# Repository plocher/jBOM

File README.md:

# jBOM — KiCad Bill of Materials and Placement Generator

## Why jBOM?

Designing a PCB in KiCad is only part of the journey that results in a fabricated and assembled electronic product.  PCB fabrication requires Gerber files; assembly requires a **Bill of Materials (BOM)** and a **Placement file (CPL/POS)**.  jBOM generates all three.

The common KiCad workflow has you annotate your KiCad symbols with supply chain details such as "IPN:RES-331-0603", "MFG:Yageo", "MPN:CC0603KRX7R9BB104", "LCSC:C123456", and then use KiCad's fabrication plugins to generate BOM and CPL files.  This mechanism is easy to understand, and, through KiCad's web/database library integration, plugins such as Part-DB, InvenTree, PartsBox and GitPLM connect to extensive parts databases.  While these this workflow has proven sufficient for many developers, it inadvertently makes it difficult to decouple supply chain evolution from a project's electronic and mechanical specifications.

**jBOM solves this** by separating part selection from circuit design. You design with generic values ("10k, 5%, Resistor_SMD:R_0603_1608Metric"), maintain a currated inventory file with your desired parts, and jBOM intelligently matches them at BOM generation time.  Changing suppliers or cost reducing a set of projects is as simple as updating an inventory spreadsheet.

## Documentation
Command line: [docs/README.man1.md](docs/README.man1.md)
Python Library API: [docs/README.man3.md](docs/README.man3.md)
KiCad Eeschema Integration: [docs/README.man4.md](docs/README.man4.md)
jBOM Inventory File Format: [docs/README.man5.md](docs/README.man5.md)

## Installation
Requires Python 3.10 or newer.

**From PyPI (recommended):**

```bash
# Basic installation (with only CSV inventory support)
pip install jbom

# With CSV, Excel and Numbers spreadsheet support
pip install jbom[all]

# With CSV and Excel support
pip install jbom[excel]
# With CSV and Apple Numbers support
pip install jbom[numbers]

# With Mouser Search support
pip install jbom[search]
```

## Quick Start

**Scenario: New KiCad project → JLCPCB manufacturing files.**

### 1. Extract an inventory template

```bash
jbom inventory MyProject/ -o inventory.csv
```

This writes one row per unique Value + Package combination found in your schematics. IPN, Category, Value, and Package are pre-filled; supplier columns (LCSC, Manufacturer, MFGPN) are blank for you to complete.

### 2. Audit schematic field quality

Before filling in part numbers, verify your schematic fields are complete:

```bash
jbom audit MyProject/ -o report.csv
```

This checks every component against jBOM's field taxonomy and writes findings to `report.csv`. Open it in a spreadsheet, fill in `ApprovedValue` for any `QUALITY_ISSUE` rows, set `Action` to `SET`, then apply the fixes back to your schematic:

```bash
jbom annotate MyProject/ --repairs report.csv
```

Once the schematic is clean, verify your inventory covers every component:

```bash
jbom audit MyProject/ --inventory inventory.csv
```

If your inventory carries `Datasheet`/`Datasheet Name` columns for a shared datasheet document library, `jbom audit` also runs read-only naming/provenance hygiene checks against them, and can check file presence against a local library checkout:

```bash
jbom audit inventory.csv --datasheet-library ~/Dropbox/workspace/SPCoast-inventory
```

To opt in to checking whether your inventory's Datasheet URLs still resolve (and get proposed upgrades for dead/impostor ones), pass `--check-urls`. This makes network requests and is off by default:

```bash
jbom audit inventory.csv --check-urls -o url_upgrades.csv
```

### 3. Fill in part numbers for JLC's LCSC supplier

An inventory file maps your generic schematic values to real parts from a supplier's catalog — in this case LCSC, which JLCPCB uses for sourcing. Open `inventory.csv` and fill in the **LCSC** column for each part you want JLCPCB to source. Set **Priority** to `1` on rows you want matched first.

To find LCSC part numbers:
- Search interactively: `jbom search "10k 0603 resistor" --supplier lcsc`
- Look up manually at [jlcpcb.com/parts](https://jlcpcb.com/parts)
- Export your JLCPCB private parts library (*User Center → My Inventory → My Parts Lib → Export*) and load it alongside: `--inventory project.csv --inventory jlc_library.xlsx`

> **Coming soon**: `jbom inventory MyProject/ --supplier lcsc --limit 3 -o inventory.csv` will search and populate part numbers automatically.

> **Curating a shared datasheet library?** Datasheet URLs encountered by `jbom search` / `jbom inventory --supplier` are automatically staged for review once you configure `datasheet_staging.staging_dir` in your own `~/.jbom/common.jbom.yaml`. `jbom inventory admit` is the gate that turns staged PDFs into a reviewed, named library: it proposes a manifest (curated name, matching inventory rows), you edit it, then `--apply` moves accepted PDFs into `datasheets/<name>.pdf` and hands back a paste-file for the `Datasheet Name` column. See [docs/reference/cli.md](docs/reference/cli.md#admit-subcommand-jbom-inventory-admit).

### 4. Generate fabrication files

Use `jbom fab` for a one-shot run that writes everything to a `production/` folder:

```bash
jbom fab MyProject/ --jlc --inventory inventory.csv
```

This produces:
```
production/
  jbom.csv                    ← BOM for JLCPCB
  cpl.csv                     ← component placement
  MyProject_1.0.zip           ← Gerber archive for upload (requires kicad-cli)
  backups/MyProject_1.0_....zip
```

Or generate files individually:
```bash
jbom bom MyProject/ --jlc --inventory inventory.csv   # writes MyProject.bom.csv
jbom pos MyProject/ --jlc                             # writes MyProject.pos.csv
jbom gerbers MyProject/ --jlc                         # writes gerbers/ (requires kicad-cli)
```
Preview without writing: `jbom bom MyProject/ --jlc --inventory inventory.csv -o console`

---

For the full step-by-step walkthrough, options, and troubleshooting tips, see the **[Tutorial series](docs/tutorial/README.md)**.

## KiCad Integration

jBOM provides a **Pcbnew ActionPlugin** (a toolbar button in the PCB editor) that generates BOM, pick-and-place (CPL), and Gerbers in one click. The plugin is distributed through KiCad's **Plugin and Content Manager (PCM)** as a separate channel from PyPI; `pip install jbom` installs the CLI and library only and does **not** register the KiCad plugin.

To install the plugin:

1. Download the latest PCM archive from GitHub's stable-name URL:
   [`https://github.com/plocher/jBOM/releases/latest/download/jbom-pcm.zip`](https://github.com/plocher/jBOM/releases/latest/download/jbom-pcm.zip)
   (GitHub redirects `releases/latest/download/<asset>` to whatever asset of that name is attached to the newest release, so the URL never needs to be edited when a new version ships.)
2. In KiCad, open **Plugin and Content Manager**, choose **Install from File…**, and select the downloaded `jbom-pcm.zip`.
3. Open the **PCB Editor** (Pcbnew); the jBOM toolbar button appears automatically. Vendored runtime dependencies ship inside the archive, so no additional `pip install` step is required inside KiCad's bundled Python.

For fabricator flags, output columns, inventory requirements, custom fabricator configuration, and troubleshooting, see [docs/reference/kicad-plugin.md](docs/reference/kicad-plugin.md).

**Legacy Eeschema BOM wrapper.** The repo also ships `kicad_jbom_plugin.py`, a thin shim that lets Eeschema's **Tools → Generate BOM** dialog call `jbom bom` for schematic-only BOM output. This path is optional and requires a one-time manual registration via Eeschema's Add-plugin dialog. See the [kicad-plugin-setup skill](.agents/skills/kicad-plugin-setup/SKILL.md) if you need it. Most users should use the PCM ActionPlugin above instead.

## Configuration

Built-in fabricator profiles: `--jlc`, `--pcbway`, `--seeed`.

To create a custom profile or configure organisation-wide defaults, see [docs/tutorial/README.documentation.md](docs/tutorial/README.documentation.md) and [docs/README.configuration.md](docs/README.configuration.md).

## Contributing

Contributions are welcome! jBOM is developed on GitHub at [github.com/plocher/jBOM](https://github.com/plocher/jBOM).

To contribute:
1. Fork the repository
2. Create a feature branch
3. Run tests locally:
   - Fast canary: `PYTHONPATH=src python -m pytest tests/unit/test_cli_help.py tests/unit/test_unified_loader.py tests/unit/test_fabricator_config_schema.py tests/unit/test_supplier_config_schema.py -q` and `PYTHONPATH=src python -m behave --format progress features/cli/basics.feature features/project/file.feature features/bom/core.feature features/pos/core.feature features/inventory/core.feature features/audit/core.feature`
   - Comprehensive: `PYTHONPATH=src python -m pytest tests/ -v` and `PYTHONPATH=src python -m behave --format progress features/`
4. Submit a pull request

Regenerate deterministic search parity artifacts (fixture-based):
`python scripts/generate_search_parity_artifacts.py`

Regenerate baseline-vs-candidate parity delta evidence:
`python scripts/generate_search_parity_delta_report.py`

See [docs/CONTRIBUTING.md](docs/CONTRIBUTING.md) for details.

**License**: MIT — See LICENSE file for full terms.
Author: John Plocher

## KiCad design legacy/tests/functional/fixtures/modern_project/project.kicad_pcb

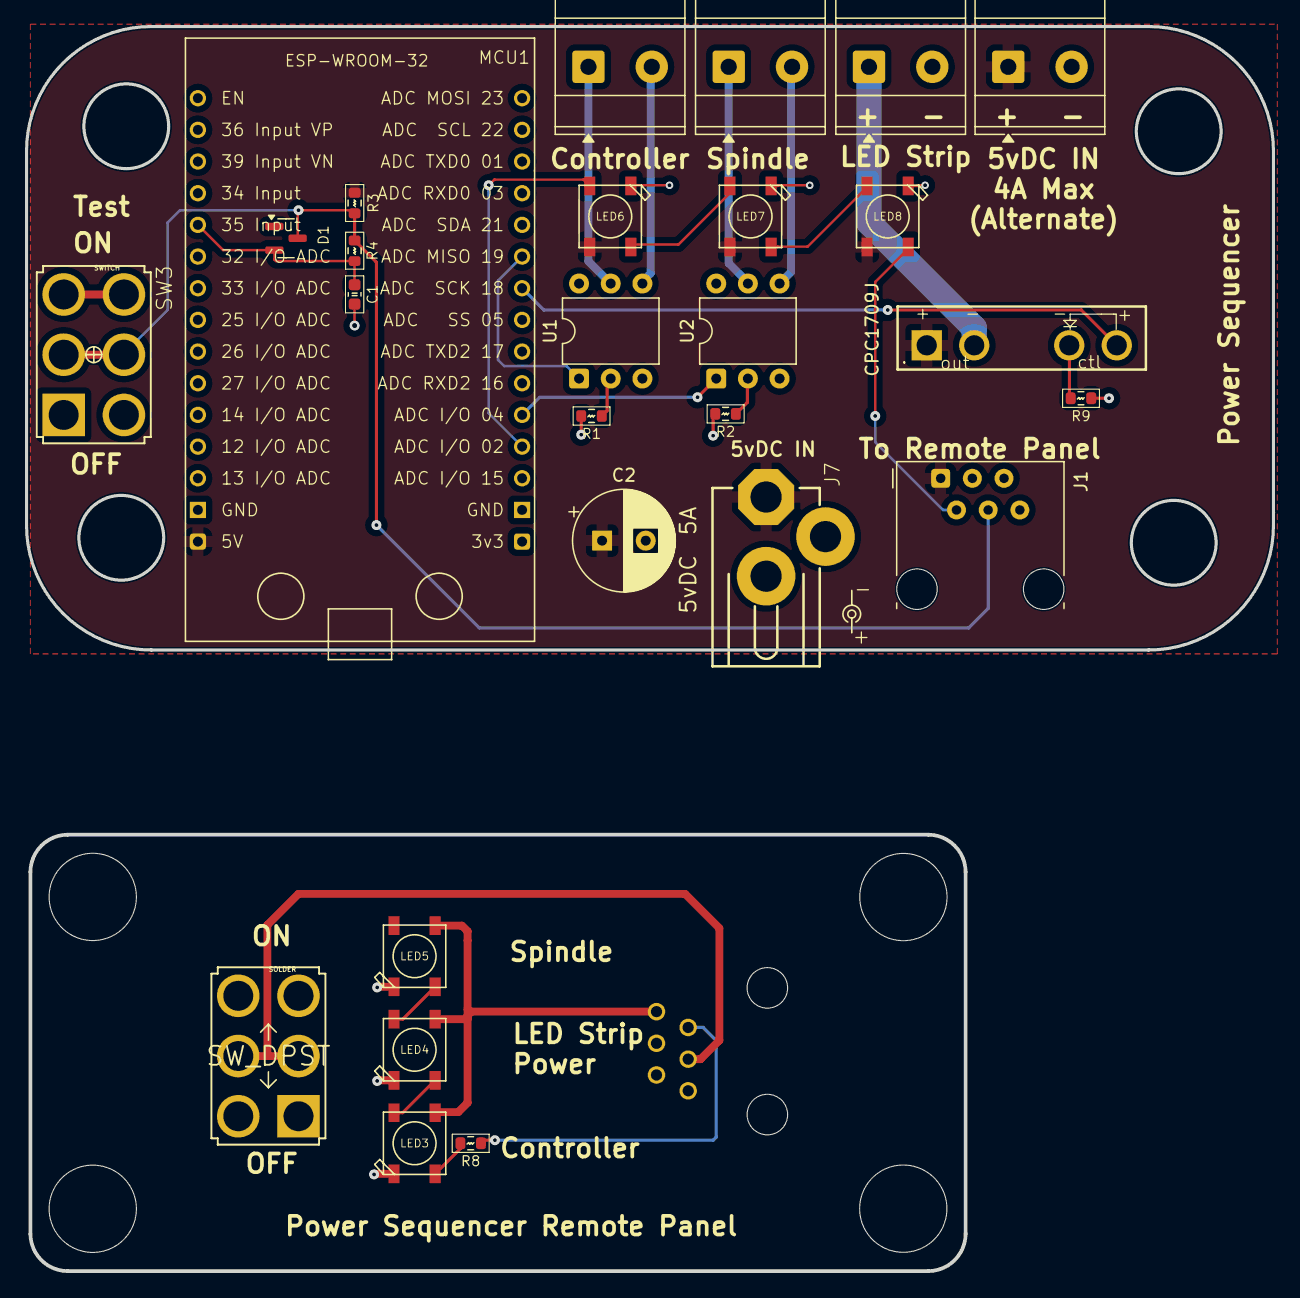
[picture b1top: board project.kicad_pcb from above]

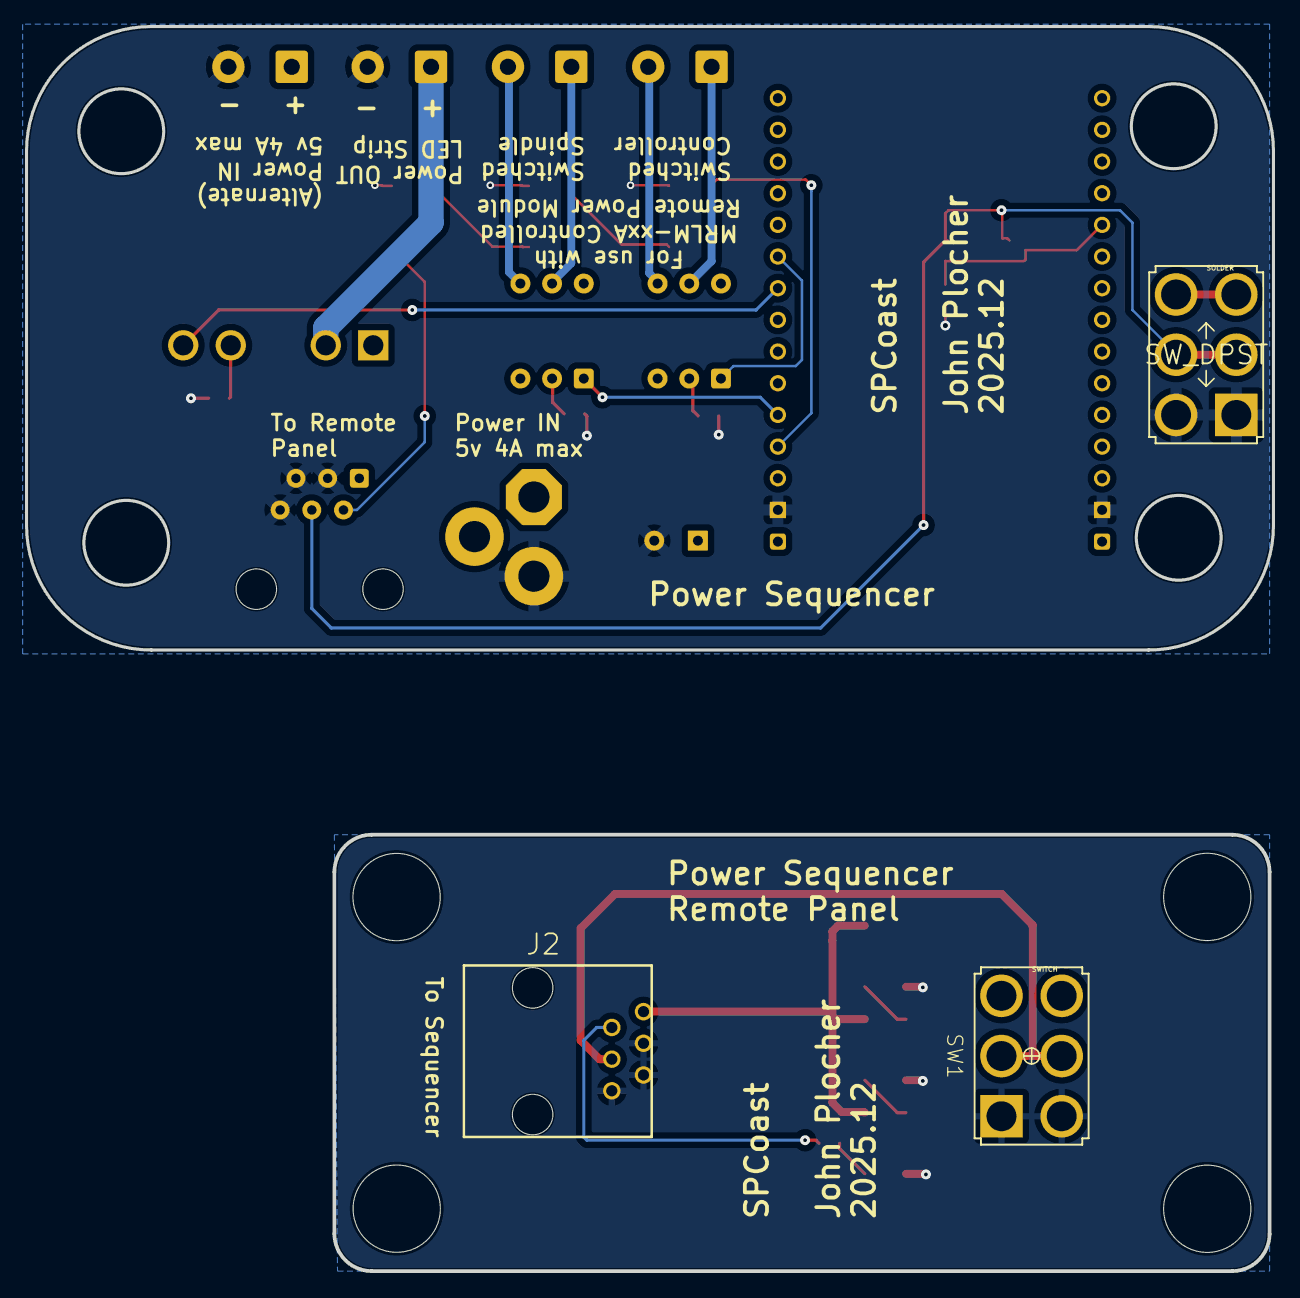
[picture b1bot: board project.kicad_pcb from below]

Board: 2 copper layers, 100.0 x 99.8 mm, 29 parts (2 on the bottom side), 26 nets.

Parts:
Board1: Board_100x050
C1: 1.0uF; 0603-CAP
C2: 1000uF; CP_Radial_D8.0mm_P3.50mm
D1: BAT54A; SOT-23
J1: Conn_6P6C; RJ12_Amphenol_54601-x06_Horizontal
J2: Conn_6P6C; RJ12_TOP
J5, J6, J8, J9: Conn_01x02; TerminalBlock_Phoenix_MKDS-3-2-5.08_1x02_P5.08mm_Horizontal
J7: DCJ0202
K1: CPC1709J; Relay_CPC1709J
LED3, LED4, LED5, LED6, LED7, LED8: WS2812B
MCU1: ESP32-DevKit-V1; ESP32_DevKit_V1
R1, R2, R8, R9: 330Ω; 0603-RES
R3: 10k0Ω; 0603-RES
R4: 22k0Ω; 0603-RES
SW1, SW3: SW_DPST; DPDT.LUGS
U1, U2: 4N28; DIP-6_W7.62mm

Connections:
+5V: C2.1, J1.1, J7.1, J9.1, K1.1 (+_1), LED6.1-VDD (VDD), LED7.1-VDD (VDD), LED8.1-VDD (VDD), MCU1.5V (+5V), R3.1
/5v: J2.1, LED3.1-VDD (VDD), LED4.1-VDD (VDD), LED5.1-VDD (VDD)
GND: C1.2, C2.2, J1.3, J1.5, J1.6, J2.3, J2.5, J2.6, J7.3, J8.2, J9.2, LED3.3-GND (GND), LED4.3-GND (GND), LED5.3-GND (GND), LED6.3-GND (GND), LED7.3-GND (GND), LED8.3-GND (GND), MCU1.GND, MCU1.GND@1 (GND), R1.2, R2.2, R9.1, SW1.1 (A), SW1.4 (A), SW3.1 (A), SW3.4 (A)
unnamed: J5.1, U2.5
unnamed: J5.2, U2.4
unnamed: J6.1, U1.5
unnamed: J6.2, U1.4
unnamed: J8.1, K1.2 (-_1)
unnamed: K1.3 (-_2), R9.2
unnamed: LED3.4-DIN (DI), R8.2
unnamed: LED3.2-DOUT (DO), LED4.4-DIN (DI)
unnamed: LED4.2-DOUT (DO), LED5.4-DIN (DI)
unnamed: LED6.2-DOUT (DO), LED7.4-DIN (DI)
unnamed: LED7.2-DOUT (DO), LED8.4-DIN (DI)
unnamed: R1.1, U1.2
unnamed: R2.1, U2.2
unnamed: SW3.3 (C), SW3.6 (C)
_neopixel: J2.2, R8.1
_switch: J2.4, SW1.2 (B), SW1.5 (B)
controller: MCU1.IO19 (GPIO19), U1.1
debounced_switch: C1.1, D1.2, MCU1.IO35 (GPIO35), R4.2
neopixel: LED6.4-DIN (DI), MCU1.IO2 (GPIO2)
neopixel_out: J1.2, LED8.2-DOUT (DO)
spindle: MCU1.IO4 (GPIO4), U2.1
ssr: K1.4 (+_2), MCU1.IO18 (GPIO18)
switch: D1.3, J1.4, R3.2, R4.1, SW3.2 (B), SW3.5 (B)

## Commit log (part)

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2026-05-09 fix(plugin): skip gerbers, use pcbnew title block directly, surface config error
    Three smoke-test fixes:
    - skip_gerbers=True: running kicad-cli subprocess from inside a KiCad plugin
    causes a hang on macOS (two KiCad instances conflict). Gerbers disabled until
    native pcbnew PLOT_CONTROLLER path is implemented.
    - Archive name: use pcbnew.GetBoard().GetTitleBlock() directly instead of
    reading from disk — faster and avoids kicad_pro filename guessing.
2026-05-09 fix(discovery): prefer directory-name .kicad_pro when multiple exist
    When a project directory contains multiple .kicad_pro files (e.g. a main
    project alongside a sub-project or variant), prefer the file whose stem
    matches the directory name — the canonical KiCad convention.
    Falls back to alphabetically first when no directory-name match exists.
    This fixes POS (CPL) generation in projects with multi-.kicad_pro dirs,
    unblocking cpl.csv output in the KiCad plugin smoke test.
2026-05-09 fix(plugin): wx.Dialog+Show() for toolbar re-invoke; Finder opens in debug mode
    Bug 1 — Finder not opening when debug=True then Close:
    _on_complete stay_open branch bound Close to lambda _e: self.Destroy()
    without calling _open_folder first. Replace with _close_and_open() closure
    that honours open_folder before destroying.
    Bug 2 — toolbar button only works once:
    wx.Frame.__init__ creates a wxFrame C++ object; KiCad's plugin framework
2026-05-10 feat(plugin): Session A POC — loadable stub ActionPlugin, options, PCM builder (#227)
    Implements issue #227 Session A scope:
    - src/jbom/plugin/__init__.py: FT-style guard registers ActionPlugin only
    inside KiCad (pcbnew in sys.modules). Safe no-op in CLI / test environments.
    sys.path bootstrap supports both PCM install (vendored jbom/) and dev-loop
    (symlink src/jbom/plugin → com_spcoast_jbom in KiCad scripting folder).
    - src/jbom/plugin/plugin.py: JBOMFabricationPlugin(pcbnew.ActionPlugin)
2026-05-10 6.55.0
    Automatically generated by python-semantic-release
2026-05-10 fix(plugin): eliminate SWIG reads + restore plot dir + auto-save after Gerbers (#255) (#258)
    * refactor(plugin): eliminate SWIG reads from archive template expansion (#255)
    Replace board.GetProject() / board.GetTitleBlock() SWIG calls with
    file-based reads in both plugin.py and dialog.py.
    Background: The dirty flag (*) appearing on ActionPlugin toolbar invocation
    is a KiCad 10 framework behavior — the C++ ActionPlugin dispatch marks the
    board modified before Run() is called, regardless of plugin code.
2026-05-10 feat(pos): rotation/offset correction service harvested from FT (#249)
    - Add src/jbom/config/transformations.csv (43 rules from Fabrication-Toolkit,
    MIT license, with attribution header; duplicates deduplicated)
    - Add RotationCorrectionService: first-match regex semantics matching FT,
    apply_rotation(normalize=) for fabricator-specific angle conventions,
    apply_offset() for centroid deltas, config search-path override support
    - Add apply_corrections: bool = False to POSRequest, FabricationRequest,
2026-05-11 6.57.0
    Automatically generated by python-semantic-release
2026-05-11 docs(adr): ADR 0008 — per-stanza id override, atomic migration, inventory deferred
    - D3: per-stanza id: override (jlc.jbom.yaml supplier stanza self-ids as lcsc;
    jbom bom --jlc and jbom search --lcsc both resolve to the same file)
    - D8: migration is atomic, no shim — loader + file migration + legacy removal
    land together; nothing has shipped, clean break requires no major bump
    - Decision Drivers: replace shim/backward-compat language with clean-break drivers
    - Decision summary and Consequences updated to match
2026-05-11 docs(adr): ADR 0009 — incorporate user edits + round 4 fixes
    User edits incorporated:
    - Renamed to strip_kicad_library_prefix_from_value (ObjC _value suffix convention)
    - D7 now shows complete definition + real jlc.jbom.yaml usage as one example
    - D1-D7 placed as subsections of Option 4; Decision section has the rationale
    Additional fixes:
    - D4 field_precedence_policy: lives in common.jbom.yaml (ambient), not
2026-05-11 docs(adr): ADR 0010 — no Field(alias) in merged code; Phase 1 is source refactor
    - D4: Field(alias=...) is a merge blocker, not a transitional tool.
    Nothing shipped externally; no justification for carrying name-mismatch
    tech debt. Rename the Python attr and update all callsites.
    - Phase 1: explicitly a three-layer source code refactoring:
    1. Config model files (fabricators/suppliers/defaults + supporting types)
    2. Python attribute renames across full codebase (bounded list from audit)
2026-05-12 feat(config): phase 1b add unified profile loader
2026-05-12 6.58.0
    Automatically generated by python-semantic-release
2026-05-12 refactor(tests): clarify profile hierarchy scenario wording
2026-05-13 test(plugin): platform-tag selector coverage and PCM build-script smoke
    tests/plugin/test_plugin_guard.py grows a TestVendorFolderTagSelector
    class covering:
    * every supported (python, OS, CPU) combo mapping to the right vendor
    folder (cp39-macosx_arm64, cp312-manylinux_aarch64, cp39-win_amd64...),
    * unsupported platforms returning None instead of crashing,
    * _vendor_pydantic_core_path() preferring an exact-tag match over the
2026-05-13 feat(plugin): platform-aware bootstrap selects matching pydantic_core
    Replace the dev-loop homebrew/user-site/venv probing with a deterministic
    per-(python, OS, CPU) selector.
    * _vendor_folder_tag() maps the running interpreter to a vendor folder name
    matching the tags produced by scripts/build_pcm_package.py (e.g.
    cp39-macosx_arm64).
    * _vendor_pydantic_core_path() prefers an exact tag match and falls back to
2026-05-13 fix(bom): BOM generation is PCB-driven (PCB-first cutover)
    BOMWorkflow now follows the per-artifact contract: PCB is the canonical
    row set, schematic is enrichment. Built on Stream 1's pcb_project_loader
    helpers so BOM and POS share identical resolve/load/enumerate plumbing
    (only the artifact_name label differs).
    Behaviour changes:
    * _generate uses resolve_pcb_input(artifact_name='BOM'); the diagnostic
2026-05-23 Fix: remove dead CLI code from issue #291
    Under the PCB-first contract (PR #289), the CLI-level footprint enforcement
    helpers are no longer invoked in the live execution path. The service-level
    equivalent (enforce_bom_device_footprints) remains exported for downstream tooling.
    Changes:
    - Delete _enforce_bom_device_footprints() from cli/bom.py (and helpers)
    - _resolve_entry_device_footprint()
2026-05-23 docs: document canonical PCB FPID in Footprint column
    Closes #297
2026-05-25 docs(247): correct target tree to 5 docs folders + .agents/skills/
    Audit doc updates to reflect the corrected skills location:
    - Target tree now shows 5 docs/ folders (was 6). Skills moved to
    .agents/skills/ (outside docs/) with docs/skills/ as a convenience
    symlink.
    - \xe2\x86\x92skill disposition target updated to
    .agents/skills/<skill-name>/SKILL.md.
2026-05-25 docs(architecture): normalize eaglelib2kicad-adapter-requirements into ADR 0016 (#300)
    Converts the pre-ADR-format service-API contract document for the
    EagleLib2KiCad adapter integration boundary into formal ADR 0016.
    Source content preserved verbatim; only ADR scaffolding headers and
    Provenance section added.
    Refs #300
    Refs #247
2026-05-25 docs(247): populate Pass-1 verdicts for all 34 files; expand findings registry F-001..F-013
    Synthesize the five sub-agent verdict reports into the audit working
    matrix. All 34 in-scope files now have per-file blocks recording
    verdict (useful/useless/mixed), charter-job mapping, audience,
    proposed disposition, one-sentence rationale, and findings.
    Verdict summary:
    - useful (keep/refresh/relocate as-is): 9
2026-05-25 docs(247): Wave A.5 \xe2\x80\x94 straggler cleanup
    Files identified during Wave A audit that were not in the original
    audit scope or had simple dispositions deferred. Resolutions:
    - features/PROJECT_INPUT_RESOLUTION_TESTS.feature - misplaced gherkin
    file relocated to features/ (where behave looks).
    - docs/dev/validation/JohnExample.csv - test-fixture CSV in docs/;
    deleted per user disposition (not retained as a fixture; the
2026-05-25 docs(247-B1-arch): split README.developer + DEVELOPER_GUIDE into design docs + skill (Wave B.1)
    Produces three new files from docs/README.developer.md and
    docs/dev/guides/DEVELOPER_GUIDE.md:
    1. docs-new/design/architecture-overview.md
    Architecture intent, module structure (f05cc6d basis), key design
    principles, hierarchical schematic support, BOM data flow, two
    matching strategies, PCB module, spreadsheet support, and component
2026-05-25 docs(247-B2-config): split README.configuration.md into design + reference (Wave B.2)
    Produces two files from docs/README.configuration.md:
    - docs-new/design/configuration-semantics.md (223 lines)
    Durable axioms: profile resolution order with priority, the
    cumulative-for-common / first-match-for-named asymmetry,
    inheritance/merge semantics (deep merge dicts, list replace,
    null deletes, circular extends rejected), field reference
2026-05-25 docs(247): delete Wave B.2 source files (8 files now superseded by docs-new/)
    Sources successfully migrated by Wave B.2 agents and verified
    content-equivalent in the new locations.
    Wave B.2 source -> destination map:
    - README.man4.md + plugin-dev-setup.md -> reference/kicad-plugin.md
    + kicad-plugin-setup skill + plugin-dev-setup skill
    - README.configuration.md -> design/configuration-semantics.md
2026-05-25 docs(reference): invert plugin-install framing — PCM is canonical, manual is fallback
    Previous revision had the framing backwards: it presented the manual
    'Eeschema -> Add plugin' dialog as the primary registration path with
    PCM-managed directories described as 'where ActionPlugins happen to
    also live'. The actual design intent is the opposite:
    - PCM is the recommended and supported install mechanism for the
    entire jBOM KiCad integration (ActionPlugin + BOM-plugin wrapper).
2026-05-26 7.0.1
    Automatically generated by python-semantic-release
2026-05-26 chore(workflow): automate post-merge branch cleanup
    Add scripts/post_merge_cleanup.py to enforce patch-equivalence checks
    before deleting local/remote branches after merge. Default output is
    quiet on the success path, with warning/error-focused messaging for
    unmerged or unsafe cases. Support optional all-branch iteration when
    --branch is omitted and --verbose diagnostics when needed.
    Update git-workflow skill and WARP.md to require scripted cleanup as
2026-05-27 docs(247-followup): reconcile field-synonyms and DNP/FPID docs from main
    Reconcile post-merge documentation drift by adding the field_synonyms
    mechanism section to configuration semantics and updating CLI/plugin/
    inventory references for current DNP and canonical PCB FPID behavior.
    Refs #312
    Refs #271
    Refs #294
2026-05-29 docs(cli): reframe promote docs around design intent
    Update CLI reference and inventory workflow tutorial language to describe promote/inventory supplier and API-key semantics as design intent instead of documenting temporary implementation boundaries.
